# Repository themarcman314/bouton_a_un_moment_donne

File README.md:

## HW prototype
kicad schematic and board files as well as BOM and step files are available here.

This code is not even in alpha.

Was trying to figure out a version name so I asked chatgpt :

This code is in "proto".

I know it might sound similar to some but dont confuse this with "production".

## Usage

### Clone the repo
HTTPS
```bash
$ git clone "https://github.com/themarcman314/bouton_a_un_moment_donne.git"
```
SSH
```bash
$ git clone git@github.com:themarcman314/bouton_a_un_moment_donne.git
```

### Wire I2S pins from ESP8266NodeMCU to MAX98357A DAC & class D amp
Kindly RTFM and follow wiring from here :
https://github.com/earlephilhower/ESP8266Audio?tab=readme-ov-file#i2s-dacs

### Flash firmware
Open `.ino` file with the arduino ide and click the arrow pointing right to flash.

### Configure audio files
1. Connect to the WAP with Wi-Fi enabled device.
SSID name is `fbi_van`

2. Portal with the configuration page should open automatically.
If not just go to `192.168.1.1` or any ip at all really.

3. Upload small mp3 files (2 MByte or smaller works well). My esp8266 module is limited to 4MB, I am allocating 3MB to the filesystem. Even when doing so, the amount of files that can be uploaded is limited depending on the bit rate, duration of audio, etc...
Remaining space is displayed on the main page.

Be patient when uploading a file.
Uploading a 1.1 MByte file took me 15 seconds which gives a transfering speed of about 1.1 * 8 / 15 = 0.58 MBit/s

Below is the configuration I set in arduino-ide to increase the upload speed

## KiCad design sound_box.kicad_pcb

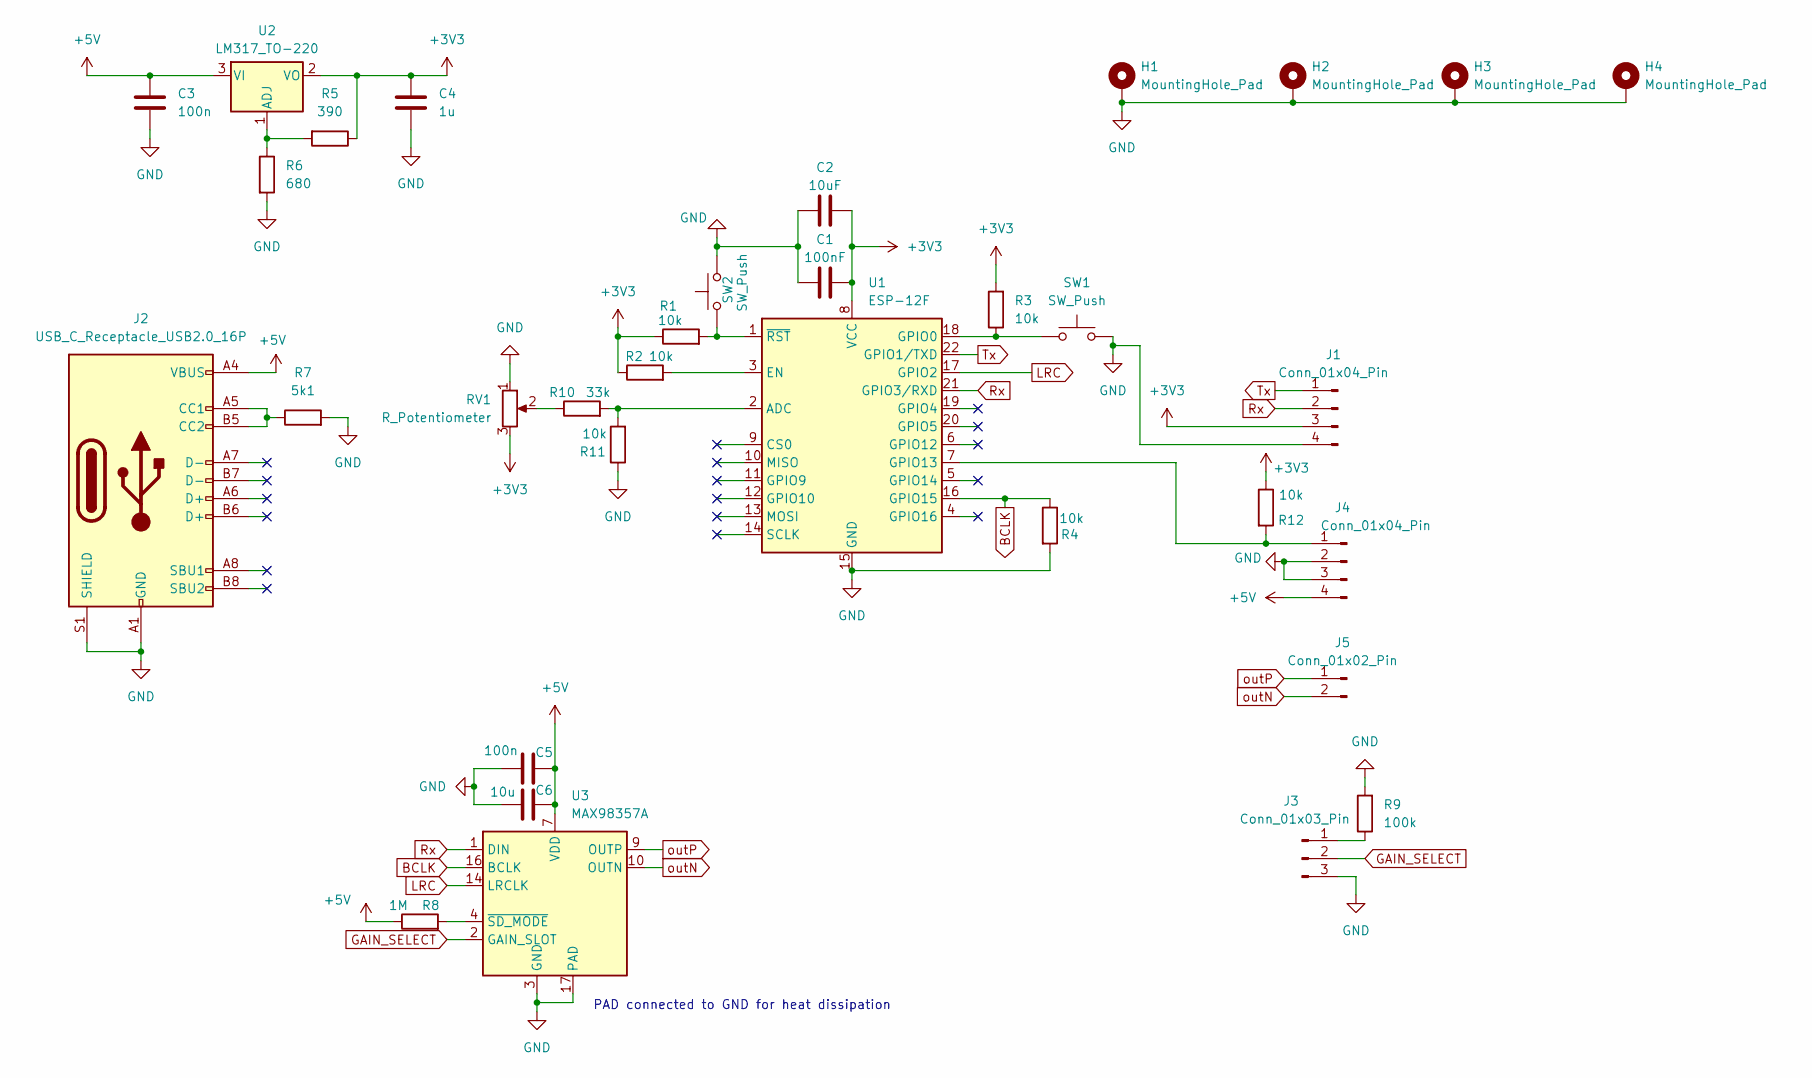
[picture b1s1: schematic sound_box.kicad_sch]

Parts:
C1: 100nF; C_0805_2012Metric_Pad1.18x1.45mm_HandSolder
C2: 10uF; C_0805_2012Metric_Pad1.18x1.45mm_HandSolder
C3, C5: 100n; C_0805_2012Metric_Pad1.18x1.45mm_HandSolder
C4: 1u; C_0805_2012Metric_Pad1.18x1.45mm_HandSolder
C6: 10u; C_0805_2012Metric_Pad1.18x1.45mm_HandSolder
H1, H2, H3, H4: MountingHole_Pad; MountingHole_2.2mm_M2_DIN965_Pad
J1, J4: Conn_01x04_Pin; PinHeader_1x04_P2.54mm_Vertical
J2: USB_C_Receptacle_USB2.0_16P; USB_C_Receptacle_HRO_TYPE-C-31-M-12
J3: Conn_01x03_Pin; PinHeader_1x03_P2.54mm_Vertical
J5: Conn_01x02_Pin; PinHeader_1x02_P2.54mm_Vertical
R1, R2, R3, R4, R11, R12: 10k; R_0805_2012Metric_Pad1.20x1.40mm_HandSolder
R5: 390; R_0805_2012Metric_Pad1.20x1.40mm_HandSolder
R6: 680; R_0805_2012Metric_Pad1.20x1.40mm_HandSolder
R7: 5k1; R_0805_2012Metric_Pad1.20x1.40mm_HandSolder
R8: 1M; R_0805_2012Metric_Pad1.20x1.40mm_HandSolder
R9: 100k; R_0805_2012Metric_Pad1.20x1.40mm_HandSolder
R10: 33k; R_0805_2012Metric_Pad1.20x1.40mm_HandSolder
RV1: R_Potentiometer; Potentiometer_Piher_T-16H_Single_Horizontal
SW1, SW2: SW_Push; SW_1825910-6-4
U1: ESP-12F; ESP-12E
U2: LM317_TO-220; TO-220-3_Vertical
U3: MAX98357A; TQFN-16-1EP_3x3mm_P0.5mm_EP1.23x1.23mm

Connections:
+3V3: C1.2, C2.2, C4.1, J1.3, R1.1, R2.1, R3.2, R5.1, R12.1, RV1.3, U1.8 (VCC), U2.2 (VO)
+5V: C3.1, C5.2, C6.2, J2.A4 (VBUS), J2.A9 (VBUS), J2.B4 (VBUS), J2.B9 (VBUS), J4.4, R8.1, U2.3 (VI), U3.7 (VDD), U3.8 (VDD)
BCLK: R4.1, U1.16 (GPIO15), U3.16 (BCLK)
GAIN_SELECT: J3.2, U3.2 (GAIN_SLOT)
GND: C1.1, C2.1, C3.2, C4.2, C5.1, C6.1, H1.1, H2.1, H3.1, H4.1, J1.4, J2.A1 (GND), J2.A12 (GND), J2.B1 (GND), J2.B12 (GND), J2.S1 (SHIELD), J3.3, J4.2, J4.3, R4.2, R6.2, R7.2, R9.2, R11.1, RV1.1, SW1.2, SW2.2, U1.15 (GND), U3.3 (GND), U3.11 (GND), U3.15 (GND), U3.17 (PAD)
LRC: U1.17 (GPIO2), U3.14 (LRCLK)
unnamed: J2.A5 (CC1), J2.B5 (CC2), R7.1
unnamed: J3.1, R9.1
unnamed: J4.1, R12.2, U1.7 (GPIO13)
unnamed: R10.1, RV1.2
unnamed: R10.2, R11.2, U1.2 (ADC)
unnamed: R2.2, U1.3 (EN)
unnamed: R3.1, SW1.1, U1.18 (GPIO0)
unnamed: R1.2, SW2.1, U1.1 (~RST)
unnamed: R5.2, R6.1, U2.1 (ADJ)
unnamed: R8.2, U3.4 (~SD_MODE)
Rx: J1.2, U1.21 (GPIO3/RXD), U3.1 (DIN)
Tx: J1.1, U1.22 (GPIO1/TXD)
outN: J5.2, U3.10 (OUTN)
outP: J5.1, U3.9 (OUTP)

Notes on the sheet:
PAD connected to GND for heat dissipation

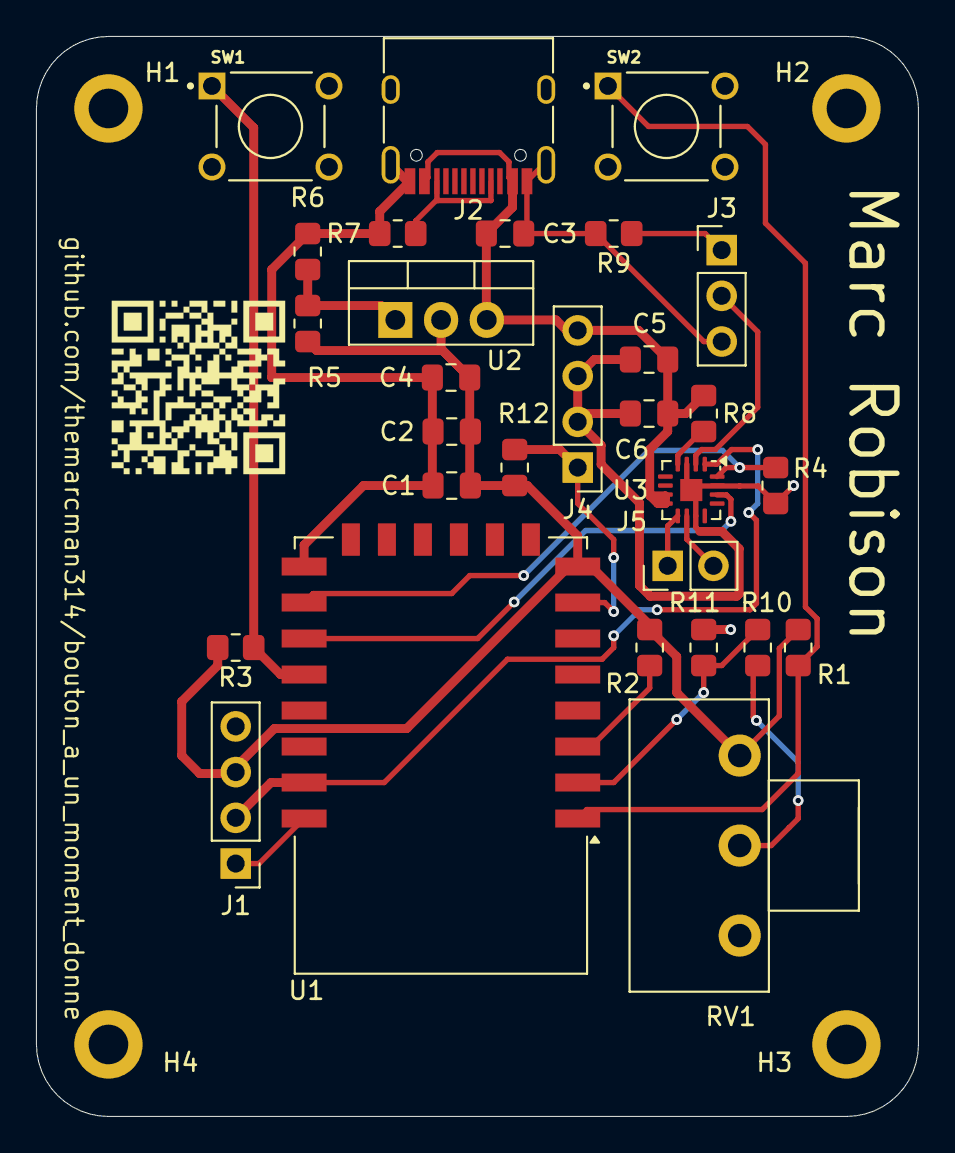
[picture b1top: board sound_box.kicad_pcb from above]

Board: 2 copper layers, 49.0 x 60.0 mm, 33 parts (0 on the bottom side), 20 nets.

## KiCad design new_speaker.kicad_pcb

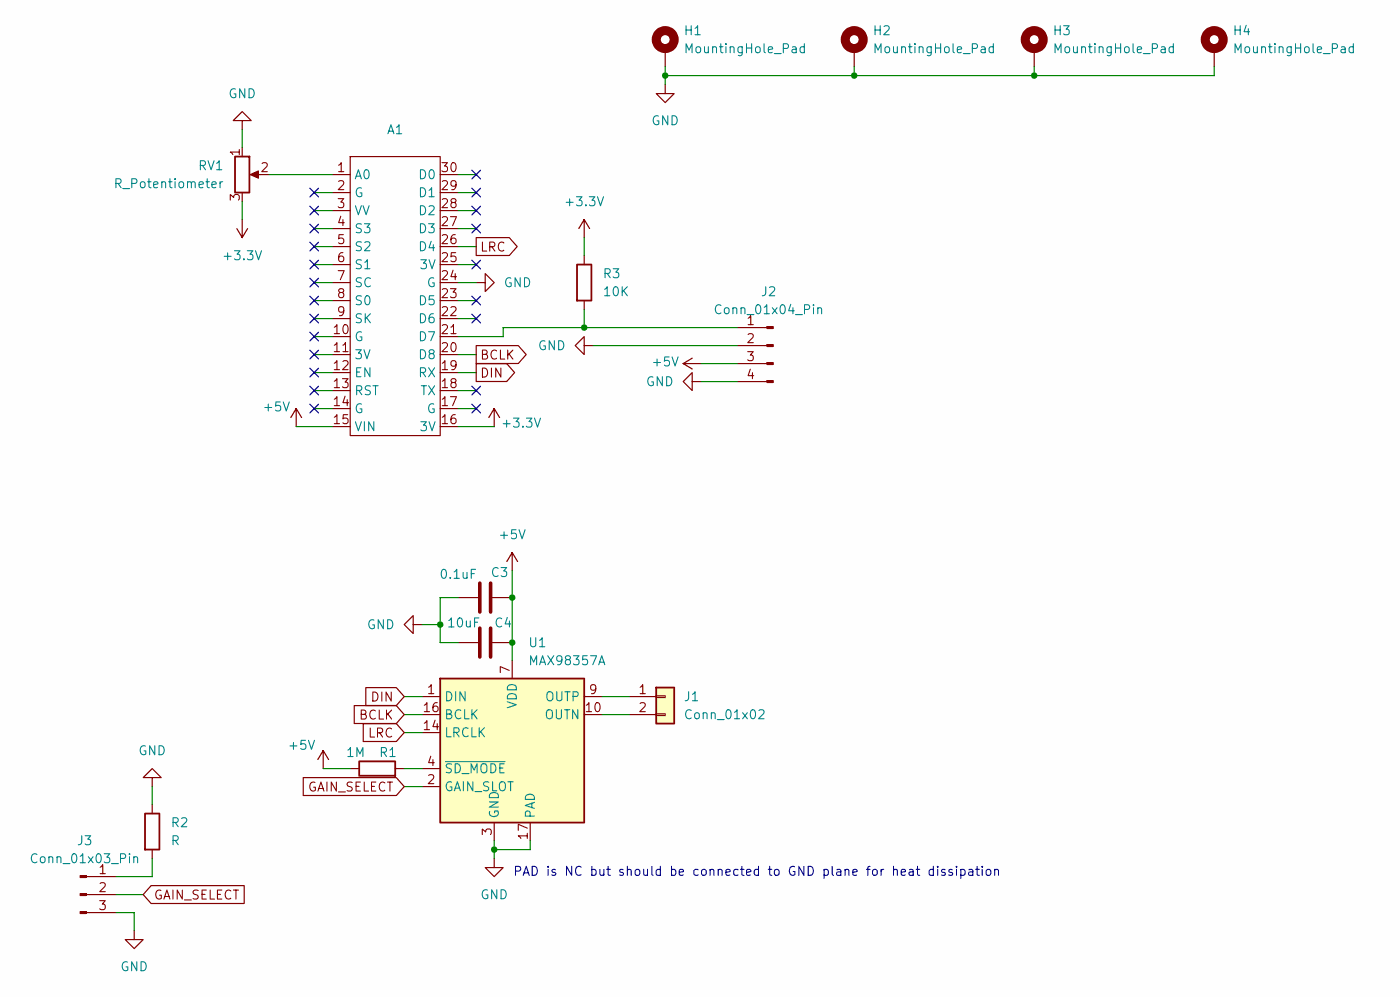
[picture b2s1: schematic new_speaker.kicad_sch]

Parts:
A1: NodeMCU-LoLinV3
C3: 0.1uF; C_0805_2012Metric_Pad1.18x1.45mm_HandSolder
C4: 10uF; C_0805_2012Metric_Pad1.18x1.45mm_HandSolder
H1, H2, H3, H4: MountingHole_Pad; MountingHole_3.2mm_M3_DIN965_Pad_TopBottom
J1: Conn_01x02; PinHeader_1x02_P2.54mm_Vertical
J2: Conn_01x04_Pin; PinHeader_1x04_P2.54mm_Vertical
J3: Conn_01x03_Pin; PinHeader_1x03_P2.54mm_Vertical
R1: 1M; R_0805_2012Metric_Pad1.20x1.40mm_HandSolder
R2: R; R_0805_2012Metric_Pad1.20x1.40mm_HandSolder
R3: 10K; R_0805_2012Metric_Pad1.20x1.40mm_HandSolder
RV1: R_Potentiometer; Potentiometer_Piher_T-16H_Single_Horizontal
U1: MAX98357A; TQFN-16-1EP_3x3mm_P0.5mm_EP1.23x1.23mm

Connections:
+3.3V: A1.16 (3V), R3.1, RV1.3
+5V: A1.15 (VIN), C3.2, C4.2, J2.3, R1.1, U1.7 (VDD), U1.8 (VDD)
BCLK: A1.20 (D8), U1.16 (BCLK)
DIN: A1.19 (RX), U1.1 (DIN)
GAIN_SELECT: J3.2, U1.2 (GAIN_SLOT)
GND: A1.24 (G), C3.1, C4.1, H1.1, H2.1, H3.1, H4.1, J2.2, J2.4, J3.3, R2.1, RV1.1, U1.3 (GND), U1.11 (GND), U1.15 (GND), U1.17 (PAD)
LRC: A1.26 (D4), U1.14 (LRCLK)
unnamed: A1.1 (A0), RV1.2
unnamed: A1.21 (D7), J2.1, R3.2
unnamed: J1.1, U1.9 (OUTP)
unnamed: J1.2, U1.10 (OUTN)
unnamed: J3.1, R2.2
unnamed: R1.2, U1.4 (~SD_MODE)

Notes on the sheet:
PAD is NC but should be connected to GND plane for heat dissipation

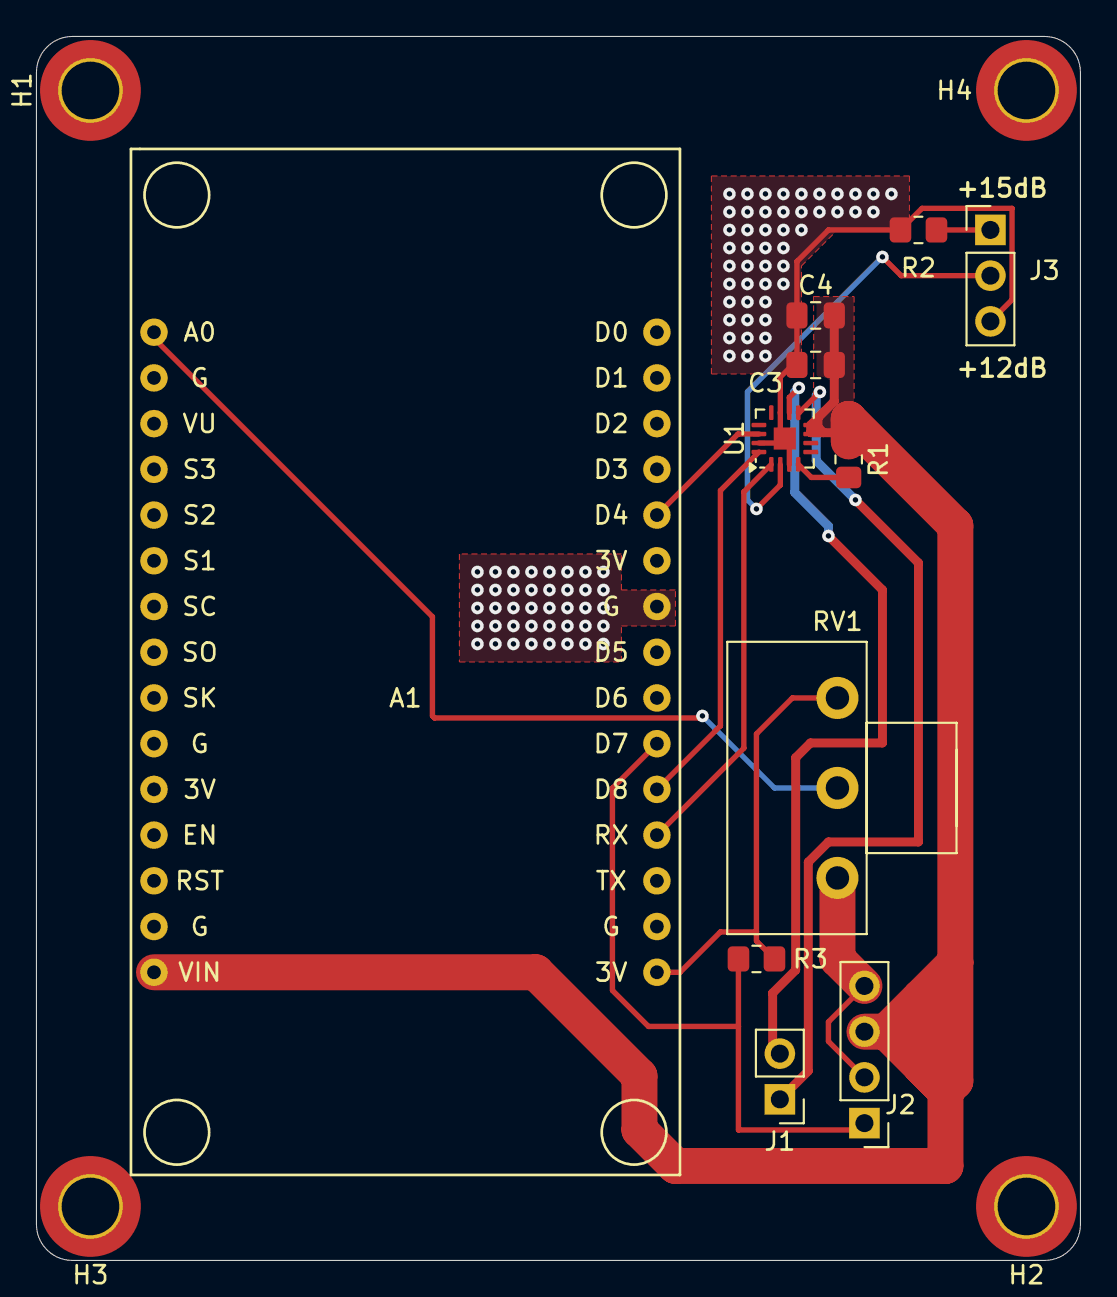
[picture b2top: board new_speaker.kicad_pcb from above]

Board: 2 copper layers, 58.0 x 68.0 mm, 15 parts (0 on the bottom side), 13 nets.

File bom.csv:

"Id";"Référence";"Empreinte";"Quantité";"Désignation";"Fournisseur et réf";
1;"J3";"PinHeader_1x03_P2.54mm_Vertical";1;"Conn_01x03_Pin";;;
2;"J2";"PinHeader_1x04_P2.54mm_Vertical";1;"Conn_01x04_Pin";;;
3;"R1";"R_0805_2012Metric_Pad1.20x1.40mm_HandSolder";1;"1M";;;
4;"C4";"C_0805_2012Metric_Pad1.18x1.45mm_HandSolder";1;"10uF";;;
5;"RV1";"Potentiometer_Piher_T-16H_Single_Horizontal";1;"R_Potentiometer";;;
6;"A1";"SEEED_113990105";1;"113990105";;;
7;"R3";"R_0805_2012Metric_Pad1.20x1.40mm_HandSolder";1;"10K";;;
8;"J1";"JST_SUR_SM02B-SURS-TF_1x02-1MP_P0.80mm_Horizontal";1;"Conn_01x02";;;
9;"U1";"TQFN-16-1EP_3x3mm_P0.5mm_EP1.23x1.23mm";1;"MAX98357A";;;
10;"R2";"R_0805_2012Metric_Pad1.20x1.40mm_HandSolder";1;"R";;;
11;"C3";"C_0805_2012Metric_Pad1.18x1.45mm_HandSolder";1;"0.1uF";;;

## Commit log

2024-06-28 combined server and file system app
2024-06-29 captive portal
2024-06-29 removed junk from captive protal part
2024-07-01 handle file upload rough outline
2024-07-01 first post request done from submitting html form
2024-07-02 upload file working even with larger files
2024-07-05 list file names
2024-07-05 file name and size in table
2024-07-05 removed comented code
2024-07-06 moved html to seperate header file
2024-07-06 max fs size but still error when sending file
2024-07-06 read file ok upload file fails
2024-07-06 changed opening file mode to w+
2024-07-06 removed littlefs.end
2024-07-06 added css
2024-07-06 added image
2024-07-07 switched to SPIFFS FS from LittleFS
2024-07-08 playing audio from web button
2024-07-08 buttons bring back home page
2024-07-08 select file to play
2024-07-08 added readme
2024-07-08 fixed readme mistake
2024-07-09 fixed image from overflowing
2024-07-11 pretty buttons
2024-07-12 new browser redirect solution for android devices
2024-07-12 added explenation for memory limitations
2024-07-12 feat: improve button styling
2024-07-12 fixup! feat: improve button styling
2024-07-14 added delete section, centered buttons
2024-07-14 corrected WPA to WAP
2024-07-14 other corrections readme
2024-07-22 fixed image not loading
2024-07-30 spinning loader no js yet
2024-08-02 fixed file upload not completing
2024-08-02 loader animation for loading of regular pages
2024-08-02 loader works for file upload
2024-08-03 checks for .mp3 file extension to play the file
2024-08-03 readme update
2024-08-04 loading animation for delete and play buttons
2024-08-04 check for valid SPIFFS filename
2024-08-07 hw prototype
2024-08-08 fixed nodemcu footprint
2024-08-08 updated 3d render for new footprint
2024-08-09 added mounting pads and rounded corners
2024-08-09 fixed button input and added gain silkscreen
2024-08-09 use actual button to play audio
2024-08-09 updated 3d file and render
2024-08-26 updated resistor value in sch
2024-10-27 working version
2025-04-13 updated pcb
2025-04-14 optimized upload speed
2025-04-14 rdme update
2025-04-14 rmde correction
2025-04-15 saves config
2025-04-16 implemented volume control
2025-04-16 stop and replay audio when pressing button again
